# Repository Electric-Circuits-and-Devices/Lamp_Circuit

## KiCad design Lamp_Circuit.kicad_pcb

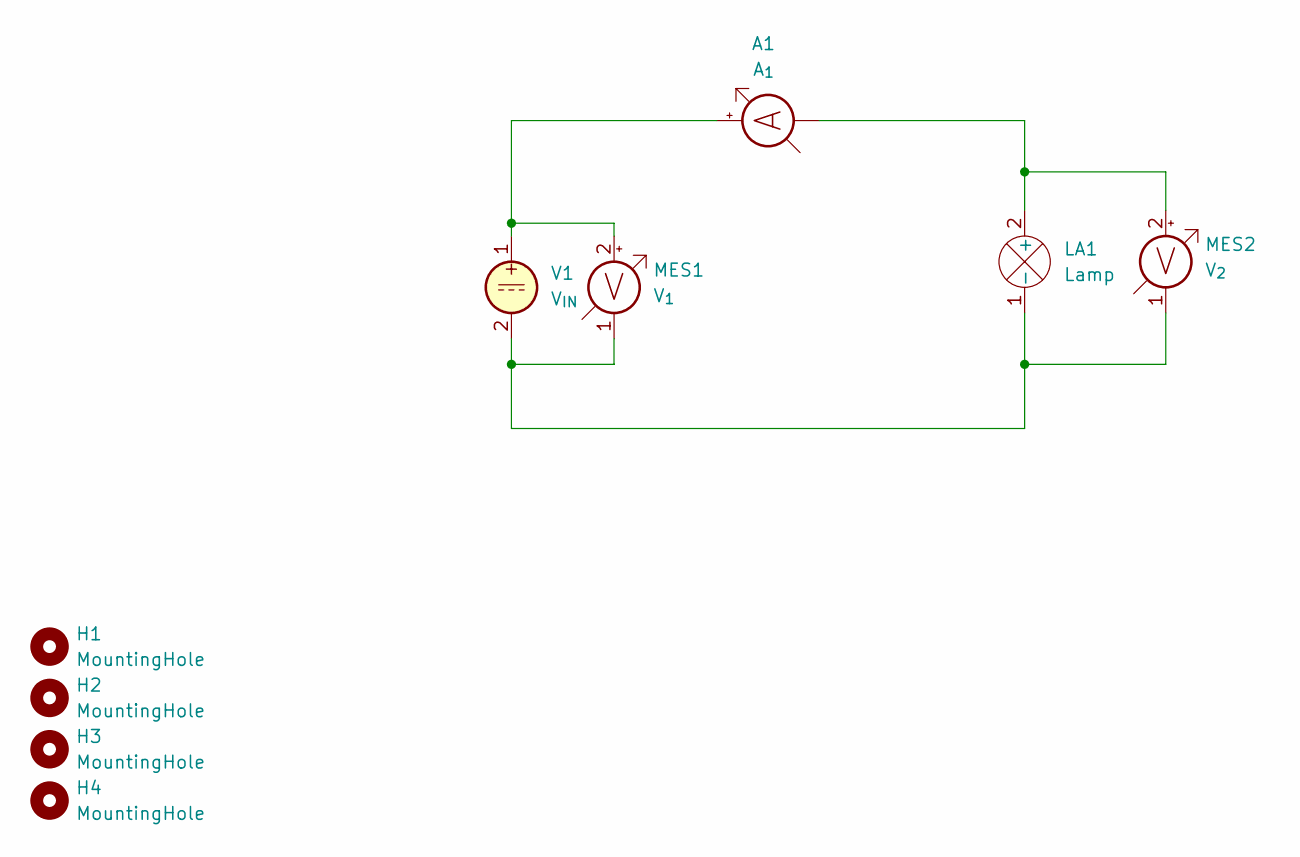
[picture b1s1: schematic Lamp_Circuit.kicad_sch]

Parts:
A1: A_{1}; Ammeter horizontal
H1, H2, H3, H4: MountingHole; MountingHole_3.2mm_M3_Pad
LA1: Lamp; Lamp_12V
MES1: V_{1}; Volt meter vertical
MES2: V_{2}; Volt meter vertical
V1: V_{IN}; DC Power Supply Vertical

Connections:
unnamed: A1.2 (+), MES1.2 (+), V1.1
unnamed: A1.1 (-), LA1.2 (+), MES2.2 (+)
unnamed: LA1.1 (-), MES1.1 (-), MES2.1 (-), V1.2

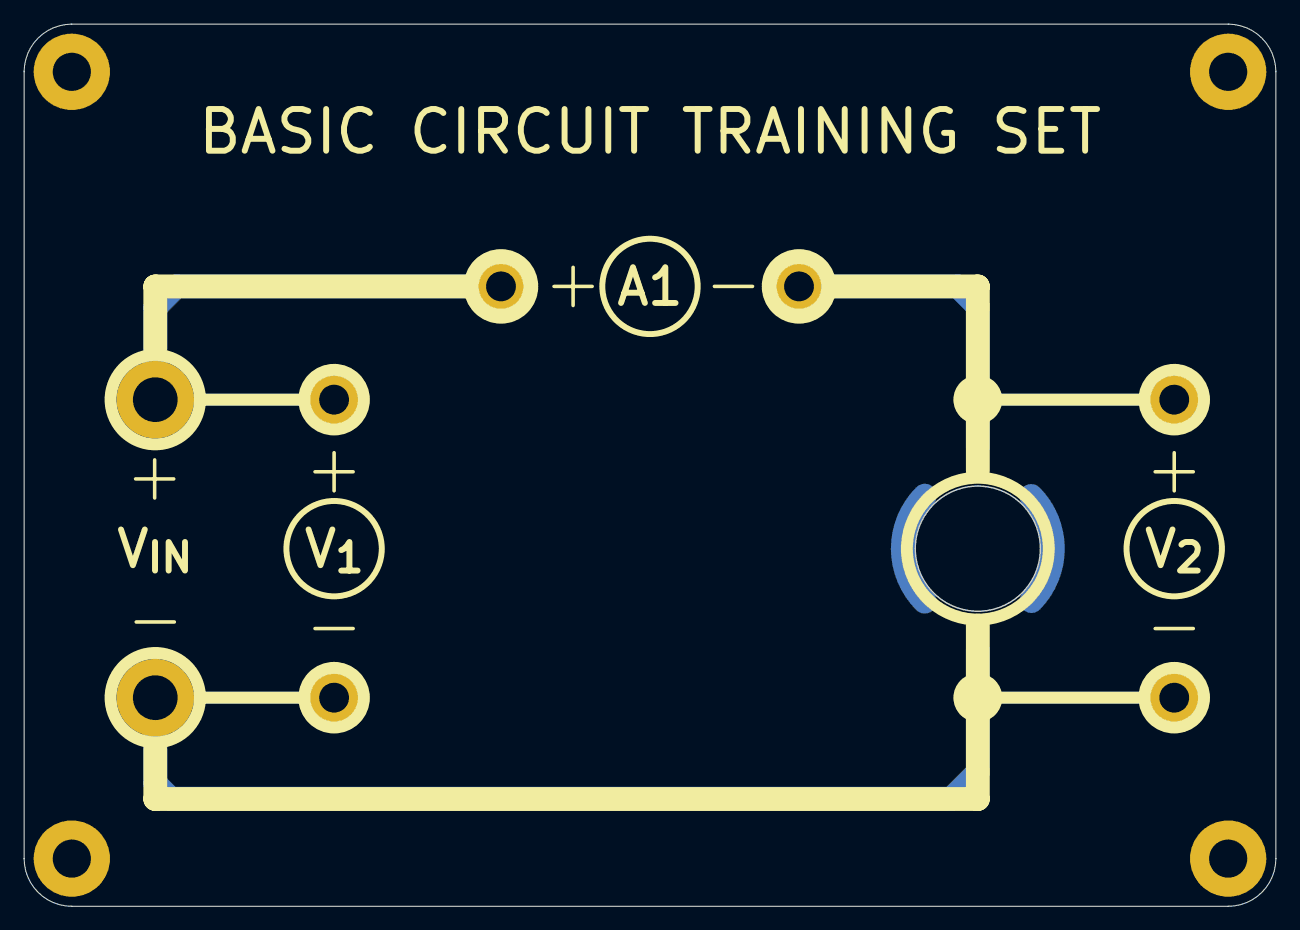
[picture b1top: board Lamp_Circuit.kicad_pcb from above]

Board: 2 copper layers, 104.9 x 73.9 mm, 9 parts (0 on the bottom side), 3 nets.
